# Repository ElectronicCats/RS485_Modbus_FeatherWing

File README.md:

# RS485 Modbus FeatherWing

A Feather board without ambition is a Feather board without FeatherWings! This is a Wing board for the SP3485 RS-485 transceiver IC, which will convert a UART serial stream to RS-485. The SP3485 is a half-duplex transceiver, so it can only communicate one way at a time, but it can reach transmission speeds of up to 10Mbps. This board requires a very low amount of power and can operate from a single +3.3VDC supply.

Works with all Feathers except for those with USB-Serial converters that use the UART pins. Right now that means the ESP8266 Huzzah Feather and nRF52832 Feather don't work.

## Features
- Fully equipped with SP3485 RS-485 transceiver and supporting components
- Operates from a single +3.3V supply
- Interoperable with +5.0V logic
- RS-485 input/output broken out to RJ-45 connector, 3.5mm screw terminal, and 0.1" pitch header
- Driver/Receiver Enable connected to RTS line
- 7V to +12V Common-Mode Input Voltage Range
- Allows up to 32 transceivers on the serial bus
- Driver Output Short-Circuit Protection

Each order comes with one assembled and tested FeatherWing, plus some header. You will need to solder in the header yourself but its a quick task.

## License

Electronic Cats invests time and resources providing this open source design, please support Electronic Cats and open-source hardware by purchasing products from Electronic Cats!

Designed by Electronic Cats.

Firmware released under an GNU AGPL v3.0 license. See the LICENSE file for more information.

Hardware released under an CERN Open Hardware Licence v1.2. See the LICENSE_HARDWARE file for more information.

Electronic Cats is a registered trademark, please do not use if you sell these PCBs.

27 May 2021

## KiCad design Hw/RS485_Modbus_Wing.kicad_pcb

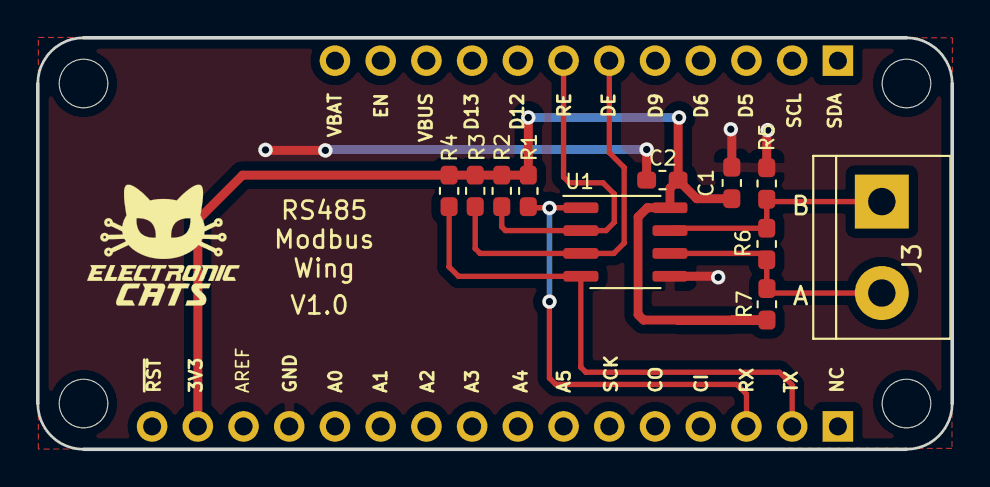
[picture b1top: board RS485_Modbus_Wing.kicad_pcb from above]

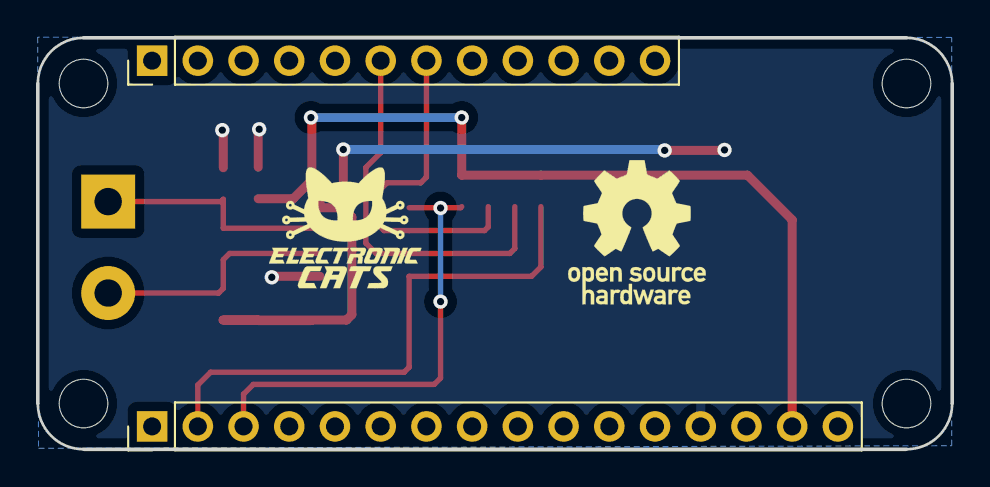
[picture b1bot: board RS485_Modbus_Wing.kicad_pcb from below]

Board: 2 copper layers, 50.8 x 22.9 mm, 13 parts (2 on the bottom side), 8 nets.

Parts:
C1: 10uF; C_0603_1608Metric_Pad1.05x0.95mm_HandSolder
C2: 0.1uF; C_0603_1608Metric_Pad1.05x0.95mm_HandSolder
J1: feather long; PinHeader_1x16_P2.54mm_Vertical
J2: feather short; PinHeader_1x12_P2.54mm_Vertical
J3: Screw_Terminal_01x02; TerminalBlock_bornier-2_P5.08mm
R1, R2, R3, R4: 10K; R_0603_1608Metric_Pad1.05x0.95mm_HandSolder
R5, R7: 20K; R_0603_1608Metric_Pad1.05x0.95mm_HandSolder
R6: 120; R_0603_1608Metric_Pad1.05x0.95mm_HandSolder
U1: SP3485EN; SOIC-8_3.9x4.9mm_P1.27mm

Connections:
+3V3: C1.1, C2.1, J1.15, R1.1, R2.1, R3.1, R4.1, R7.2, U1.8
/DE: J2.6, R3.2, U1.3
/RE: J2.7, R2.2, U1.2
/RS485A: J3.2, R6.2, R7.1, U1.6
/RS485B: J3.1, R5.2, R6.1, U1.7
/RX: J1.3, R1.2, U1.1
/TX: J1.2, R4.2, U1.4
GND: C1.2, C2.2, J1.13, R5.1, U1.5

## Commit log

2020-10-29 Schematic
2020-11-03 Last_Change_Sch
2020-11-03 Add_netlist
2020-11-03 Fist_PCB
2020-11-04 Add_Logo
2020-11-06 Last_Revision
2020-11-06 change_pin
2020-11-06 Add_Label
2020-11-09 ChangeRS
2020-11-10 Move_capacitor
2020-11-10 Labels
2020-11-10 Add_BOM
2020-11-10 fix labels and logos
2020-11-10 Add_item
2020-11-26 Change_conection
2020-11-26 Change_labels
2020-11-27 Add_test
2020-11-30 fix layout
2020-12-01 add solder mask clearence
2021-04-29 Add_3D_Model
2021-05-27 Update names for examples
2021-05-28 Update_examples
2022-01-07 Update_Kicad_6
2023-01-23 BOM update and generated
